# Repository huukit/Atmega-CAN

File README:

# This is the public repository for proximia.fi. #
Any code here is licensed under GPL/LGPL.

## Projects: ##
### Can bootloader ###
### Libraries ###
### Can Bridge CAN-USB converter ###
### Schematics ###

For more information, please browse the project documentation.
Documentation can be generated from the sources with Doxygen.

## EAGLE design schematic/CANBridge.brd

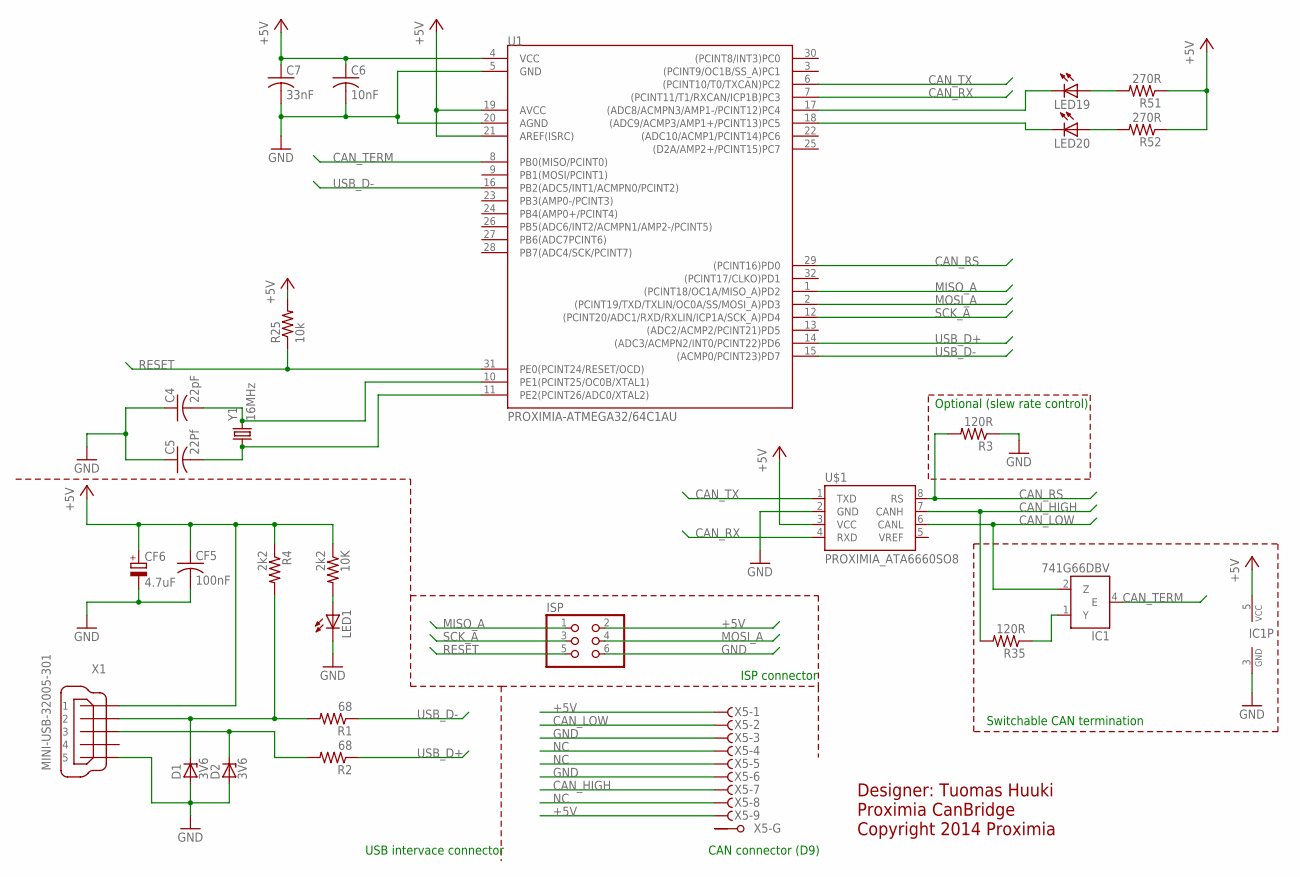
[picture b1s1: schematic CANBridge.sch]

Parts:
10K: 2k2; R0603
C4: 22pF; C0603
C5: 22Pf; C0603
C6: 10nF; C0603
C7: 33nF; C0603
CF5: 100nF; C0603
CF6: 4.7uF; PANASONIC_B
D1, D2: 3V6; SOD80C
IC1: 741G66DBV; SOT23-5
ISP: PINHD-2X3; 2X03
LED1, LED19, LED20: LEDSML1206; SML1206
R1, R2: 68; R0603
R3, R35: 120R; R0603
R4: 2k2; R0603
R25: 10k; R0603
R51, R52: 270R; R0603
U1: PROXIMIA-ATMEGA32/64C1AU; PROXIMIA_TQFP32-08
U$1: PROXIMIA_ATA6660SO8; PROXIMIA_SO08
X1: MINI-USB-32005-301; 32005-301
X5: F09HPS; F09HP
Y1: 16MHz; CRYSTAL-SMD-5X3

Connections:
+5V: 10K.1, C6.1, C7.1, CF5.1, CF6.+, IC1.5 (VCC), ISP.2, R4.1, R25.2, R51.1, R52.1, U1.4 (VCC), U1.19 (AVCC), U1.21 (AREF(ISRC)), U$1.3 (VCC), X1.1, X5.1 (F), X5.9 (F)
CAN_HIGH: R35.2, U$1.7 (CANH), X5.7 (F)
CAN_LOW: IC1.2 (Z), U$1.6 (CANL), X5.2 (F)
CAN_RS: R3.2, U1.29 ((PCINT16)PD0), U$1.8 (RS)
CAN_RX: U1.7 ((PCINT11/T1/RXCAN/ICP1B)PC3), U$1.4 (RXD)
CAN_TERM: IC1.4 (E), U1.8 (PB0(MISO/PCINT0))
CAN_TX: U1.6 ((PCINT10/T0/TXCAN)PC2), U$1.1 (TXD)
GND: C4.1, C5.1, C6.2, C7.2, CF5.2, CF6.-, D1.A, D2.A, IC1.3 (GND), ISP.6, LED1.C, R3.1, U1.5 (GND), U1.20 (AGND), U$1.2 (GND), X1.5, X5.3 (F), X5.6 (F)
MISO_A: ISP.1, U1.1 ((PCINT18/OC1A/MISO_A)PD2)
MOSI_A: ISP.4, U1.2 ((PCINT19/TXD/TXLIN/OC0A/SS/MOSI_A)PD3)
unnamed: 10K.2, LED1.A
unnamed: D1.C, R1.2, R4.2, X1.2
unnamed: D2.C, R2.2, X1.3
unnamed: C4.2, U1.10 (PE1(PCINT25/OC0B/XTAL1)), Y1.3 (2)
unnamed: C5.2, U1.11 (PE2(PCINT26/ADC0/XTAL2)), Y1.1
unnamed: IC1.1 (Y), R35.1
unnamed: LED19.A, R51.2
unnamed: LED20.A, R52.2
unnamed: LED19.C, U1.17 ((ADC8/ACMPN3/AMP1-/PCINT12)PC4)
unnamed: LED20.C, U1.18 ((ADC9/ACMP3/AMP1+/PCINT13)PC5)
NC: X5.4 (F), X5.5 (F), X5.8 (F)
RESET: ISP.5, R25.1, U1.31 (PE0(PCINT24/RESET/OCD))
SCK_A: ISP.3, U1.12 ((PCINT20/ADC1/RXD/RXLIN/ICP1A/SCK_A)PD4)
USB_D+: R2.1, U1.14 ((ADC3/ACMPN2/INT0/PCINT22)PD6)
USB_D-: R1.1, U1.15 ((ACMP0/PCINT23)PD7), U1.16 (PB2(ADC5/INT1/ACMPN0/PCINT2))

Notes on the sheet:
Optional (slew rate control)
Switchable CAN termination
USB intervace connector
CAN connector (D9)
ISP connector
Designer: Tuomas Huuki Proximia CanBridge Copyright 2014 Proximia

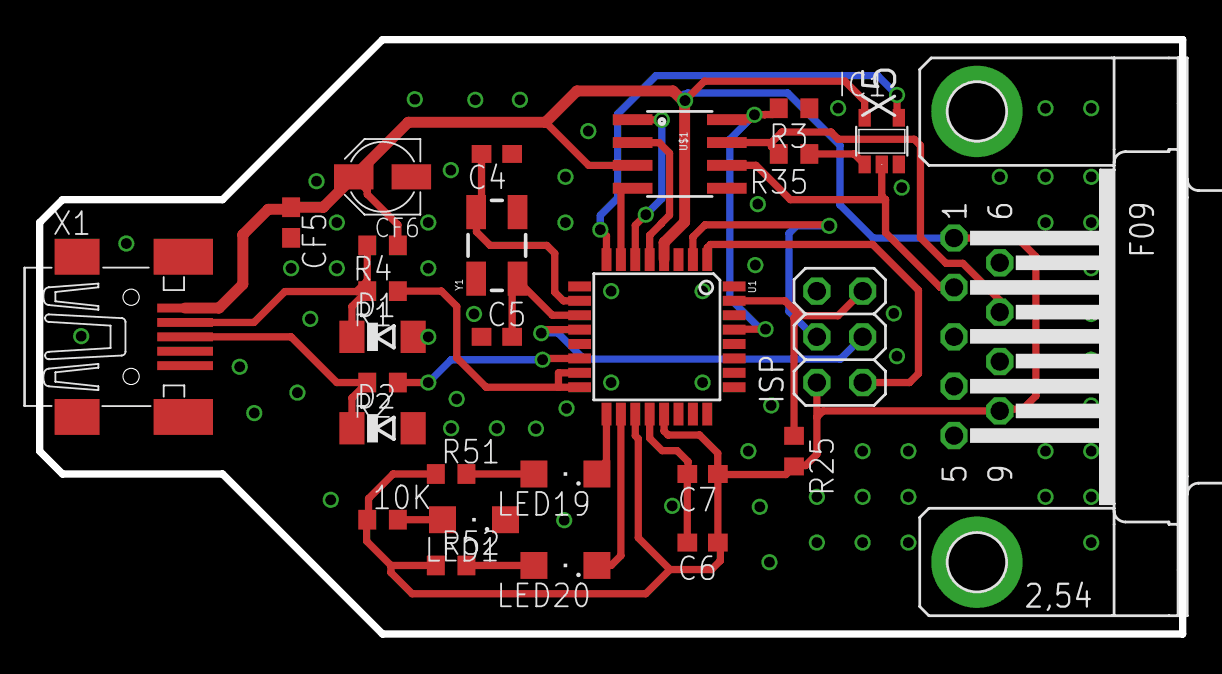
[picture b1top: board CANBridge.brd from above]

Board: 2 copper layers, 63.5 x 33.0 mm, 27 parts (0 on the bottom side), 25 nets.

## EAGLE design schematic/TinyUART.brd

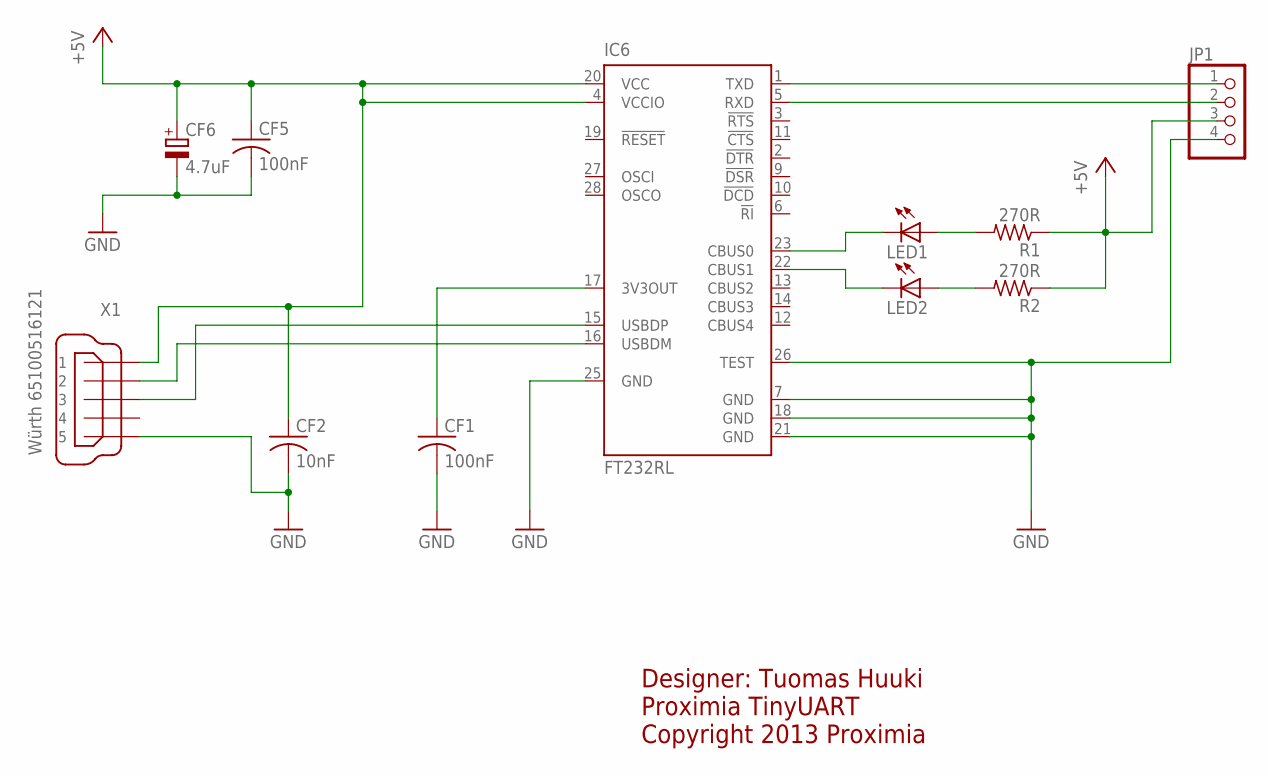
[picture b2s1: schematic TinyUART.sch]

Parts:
CF1, CF5: 100nF; C0603
CF2: 10nF; C0603
CF6: 4.7uF; PANASONIC_B
IC6: FT232RL; SSOP28
JP1: PINHD-1X4; 1X04
LED1, LED2: LEDSML1206; SML1206
R1, R2: 270R; R0603
X1: Würth 65100516121; 32005-301

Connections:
+5V: CF2.1, CF5.1, CF6.+, IC6.4 (VCCIO), IC6.20 (VCC), JP1.3, R1.1, R2.1, X1.1
GND: CF1.2, CF2.2, CF5.2, CF6.-, IC6.7 (GND), IC6.18 (GND), IC6.21 (GND), IC6.25 (GND), IC6.26 (TEST), JP1.4, X1.5
unnamed: IC6.1 (TXD), JP1.1
unnamed: IC6.5 (RXD), JP1.2
unnamed: IC6.15 (USBDP), X1.3
unnamed: IC6.16 (USBDM), X1.2
unnamed: LED1.A, R1.2
unnamed: LED2.A, R2.2
unnamed: IC6.23 (CBUS0), LED1.C
unnamed: IC6.22 (CBUS1), LED2.C
unnamed: CF1.1, IC6.17 (3V3OUT)

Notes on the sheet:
Designer: Tuomas Huuki Proximia TinyUART Copyright 2013 Proximia

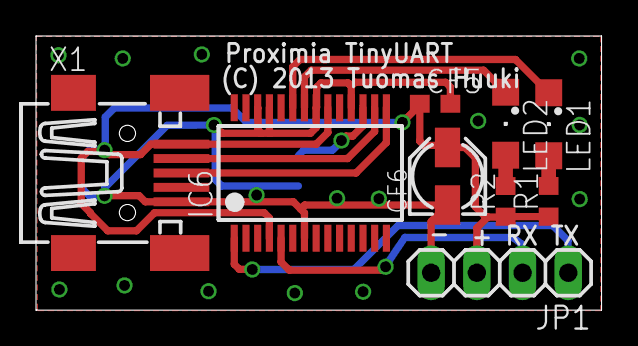
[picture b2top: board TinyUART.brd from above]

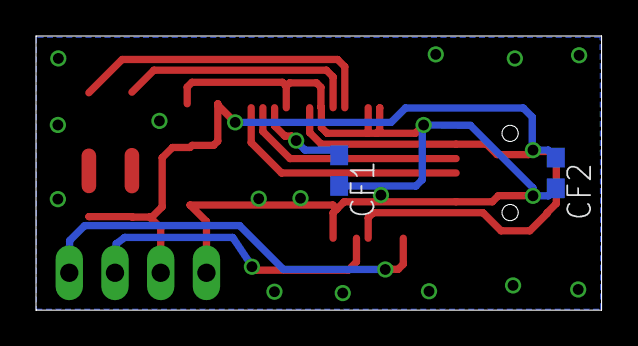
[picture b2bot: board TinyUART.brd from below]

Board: 2 copper layers, 31.4 x 15.2 mm, 11 parts (2 on the bottom side), 11 nets.

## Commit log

2014-08-03 Initial commit of files.
2014-08-03 Updating documentation.
2014-08-05 Documentation update.
2014-08-05 Documentation.
2014-08-05 More documentation.
2014-08-06 Canlib documentation.
2014-08-07 Adding TinyUART.
2014-08-24 Adding missing include. Removing #error.
2014-08-24 Fixed a bug where the page could be changed by the RX interrupt if a transmission was ongoing.
2014-08-24 Bugfix comment.
2014-09-14 Fixed a bug where an error message was sent even on a successful command request.
2014-09-21 Adding CanBridge basic project and UART library fot ATMEGA64C1.
2014-10-04 Added a missing include and also changed the canlibraryconfiguration.h to canlibraryconfiguration_base.h to make sure the correct file is included.
2014-10-04 Added return value.
2014-10-05 Support for nested interrupts. Default: off.
2014-10-05 Fixed a bug where the cantime was not copied when getting a message.
2014-10-05 Added functionality to close driver.
2014-10-05 Adding vusb-20121206 to 3rd party libraries.
2014-10-05 Ringbuffer position set needs to be atomic. It is ok to read the buffer with interrupts enabled.
2014-10-06 Very crude and simple to test the CanBridge hardware (but it works for now).
2014-10-06 Initial CANBridge schematic and board.
2014-10-06 Updated documentation and generation file.
2014-10-10 Added a debug output to make it easier to see the module boot.
2014-10-10 Restructuring project.
2014-10-10 Updating solution and project files to reflect new location.
2014-10-10 Adding initial Windows-library files. I'm not a huge fan of adding binaries to the source control but as this will be using a precompiled version of LibUSB I think that the exception is justified.
2014-10-10 Adding ignore for pro.user files.
2014-10-11 Removed qt-dependent code from header.
2014-10-11 Working on the library. USB init works.
2014-10-11 Adding class that will communicate with the device.
2014-10-14 Working on the device library.
2014-10-14 Continuing work on library. Hiding the QT implementation. Library can now receive messages and will use a callback function to inform the user of a received message.
2014-10-14 Variable intitialization fix.
2014-10-16 Prevent crash if device is not found.
2014-10-16 Adding driver.
2014-10-17 Added a way to query free TX buffers.
2014-10-17 Sends a message via API. Again, mostly proof-of-concept code at this point.
2014-10-18 Fixed a race condition in the can library.
2014-10-18 Fixed a bug where the interrupt for USB would not be served if there were messages in the buffer when initializing.
2014-10-18 QT-implementation added. Enable/disabel with #define.
2014-10-19 Compileable QT-support.
2014-10-19 Adding some ignores.
2014-10-19 Simple trace output added.
2014-10-19 Added some comments and functionality to the UI.
2014-10-22 Updating driver files.
2014-10-22 Back to QT 5.3
2016-03-17 Convert svn:ignore properties to .gitignore.
2016-05-30 Added readme for github
2017-05-15 Improving the readme file.
2017-05-15 Documentation updates.
2017-05-15 More documentation updates.
2017-05-15 Made sure everything compiles and works with QT5.8. Updated the doc, added some instruction on how to work with the libraries.
2017-05-16 Readme updated.
2017-05-16 Updated the bootloader project file to work with current versions of Atmel Studio. Added screenshots of pictures to the readme.
2017-05-16 Fixed picture links.
2017-05-16 Updated readme.
2017-05-16 Updated canbridge project to work with newer Atmel Studio.
2017-05-16 Added more info to help with the bootloader.
2017-05-16 Added spacing.
2017-05-16 Added more instructions for the bootloader.
2017-05-16 Added binaries for easy flashing.

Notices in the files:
schematic/CANBridge.brd:
(c) 2014 Tuomas Huuki
schematic/TinyUART.brd:
(C) 2013 Tuomas Huuki
parts and their libraries:
SparkFun-FreqCtrl: Licensing: CC v3.0 Share-Alike You are welcome to use this library for commercial purposes.
